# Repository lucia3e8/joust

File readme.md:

# joust!
- [ ] wands
    - [ ] enclosure design - 3d printed
    - [ ] electronics 
- [ ] base station
    - [ ] electronics

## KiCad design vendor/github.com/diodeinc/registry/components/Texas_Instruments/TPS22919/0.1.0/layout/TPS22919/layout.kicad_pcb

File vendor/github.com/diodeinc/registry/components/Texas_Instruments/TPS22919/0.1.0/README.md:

# TPS22919 — TI 5.5 V, 1.5 A load switch with controlled slew rate (SC-70-6)

Single gated power rail: TPS22919 plus input/output bypass, the QOD strap
that sets off-state discharge, and an external ON pull-down that makes the
rail default-off when nothing drives the enable.

## Parts

| `automotive` | MPN | Grade | Sourcing alternates |
|---|---|---|---|
| `False` (default) | TPS22919DCKR | catalog, −40 to 105 °C | TPS22919DCKT (250-pc reel) |
| `True` | TPS22919QDCKRQ1 | AEC-Q100 grade 1, −40 to 125 °C | — |

Both are SC-70-6 (DCK) with identical pinout and specifications. Slew rate
is fixed silicon; TI has no pin-compatible SC-70-6 sibling with a different
rise time. TPS22917 / TPS22918 add a CT pin for adjustable rise time but are
SOT-23-6 with a different pinout, so they need a separate package.

## Configuration

| Config | Type | Default | Effect |
|---|---|---|---|
| `automotive` | bool | `False` | Selects the AEC-Q100 orderable |
| `discharge` | `Internal` / `External` / `Off` | `Internal` | QOD strap: 0 Ω to VOUT, `r_qod` in series, or depopulated |
| `r_qod` | Resistance | `1kohm` | Series QOD resistance when `discharge="External"` |
| `c_in` | Capacitance | `1uF` | Input bypass (0402, 10 V) |
| `c_out` | Capacitance | `1uF` | Local output bypass (0402, 10 V); sets inrush = C × slew rate |
| `on_pulldown` | bool | `True` | Populate R_ON_PD |
| `on_pulldown_resistance` | Resistance | `100kohm` | R_ON_PD value |

## Examples

```zen
TPS22919 = Module("github.com/diodeinc/registry/components/Texas_Instruments/TPS22919/TPS22919.zen")

# microSD slot VDD, gated by an MCU GPIO. Default-off, fast discharge.
TPS22919(
    name="U_SD_PWR",
    VIN = V3V3,
    VOUT = V3V3_SD,
    GND = GND,
    ON = SD_PWR_EN,
)

# 5 V LED domain: extra local bulk, still discharged on gate-off.
TPS22919(
    name="U_LED_PWR",
    c_out = "10uF",
    VIN = V5,
    VOUT = V5_LED,
    GND = GND,
    ON = LED_PWR_EN,
)

# Slow the fall for power-down sequencing (R_DIS = 24 Ohm + r_qod).
TPS22919(
    name="U_SAT_PWR",
    discharge = "External",
    r_qod = "1kohm",
    VIN = V3V3,
    VOUT = V3V3_SAT,
    GND = GND,
    ON = SAT_PWR_EN,
)
```

## Integration notes

- `ON` thresholds (V_IH ≥ 1 V, V_IL ≤ 0.35 V) are referenced to GND, not
  VIN, so a 3.3 V GPIO can gate a 5 V rail. Keep V_ON ≤ 6 V.
- Default-off comes from the populated 100 kΩ R_ON_PD, not from the IC's
  Smart Pull Down, which disconnects permanently once ON is first driven
  high. Expect 33 µA at 3.3 V (55 µA at 5.5 V) of extra GPIO drive current
  while the rail is enabled.
- Turn-on takes 1.75–1.95 ms with a 2.7–3.2 mV/µs ramp. Inrush is
  C_LOAD × slew rate, so size total downstream bulk against what the
  upstream rail tolerates (47 µF ≈ 150 mA at 5 V).
- Off-state input current is 2 nA typ (800 nA max over temperature). There
  is no reverse blocking: the pass FET body diode conducts OUT → IN, so do
  not back-drive VOUT above VIN.
- 1.5 A continuous is a thermal limit, not an R_ON limit: R_θJA is
  210.7 °C/W in SC-70-6. Give the VIN/VOUT copper area at 1 A and above.
- The bundled `layout/TPS22919` fragment routes VIN, VOUT, QOD, and ON
  locally with 0.4 mm power copper and ties C_IN and R_ON_PD grounds
  together. C_OUT's ground pad is left for the parent board's ground plane.

## Package

**DCK / SC-70-6** (JEDEC MO-203 AB), 2.0 × 2.1 mm body, 0.65 mm pitch.
Footprint is KiCad's stock `SOT-363_SC-70-6` with an embedded STEP model —
1.025 × 0.35 mm pads on a 1.675 mm span, IPC-7351 nominal density. TI's
DCK0006A land pattern uses 0.9 × 0.4 mm pads on a 2.2 mm span; both reach a
3.1 mm outer envelope, with the KiCad pattern trading toe extension for
heel coverage.

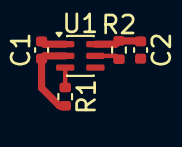
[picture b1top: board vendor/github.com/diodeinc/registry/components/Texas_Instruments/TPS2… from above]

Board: 2 copper layers, 5 parts (0 on the bottom side), 5 nets.

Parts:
C1, C2: GRM155Z71A105KE01D; C_0402_1005Metric
R1: ERJ-2RKF1003X; R_0402_1005Metric
R2: ERJ-2GE0R00X; R_0402_1005Metric
U1: TPS22919DCKR; SOT-363_SC-70-6

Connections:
GND: C1.2, C2.2, R1.2, U1.2
ON: R1.1, U1.3
QOD: R2.2, U1.5
VIN: C1.1, U1.1
VOUT: C2.1, R2.1, U1.6

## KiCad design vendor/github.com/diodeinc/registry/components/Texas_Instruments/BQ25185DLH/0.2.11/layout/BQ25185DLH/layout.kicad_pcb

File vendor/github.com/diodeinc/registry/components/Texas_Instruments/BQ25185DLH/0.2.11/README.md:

# BQ25185DLH

Texas Instruments BQ25185 1-cell, 1 A standalone **linear** Li-ion /
Li-poly / LiFePO₄ battery charger with integrated power path, pushbutton
input, and battery-tracking VINDPM. WSON-10 (DLH, 2.2 × 2.0 mm, exposed
pad). Orderable MPN: `BQ25185DLHR`.

- **VIN**: 2.7 V – 5.5 V recommended (25 V tolerant abs max)
- **ICHG**: 10 mA – 1000 mA, resistor programmed (R_ISET)
- **VBATREG**: 3.6 / 3.65 / 4.05 / 4.1 / 4.2 / 4.35 / 4.4 V (strap programmed)
- **ILIM**: 100 / 500 / 1100 mA (strap programmed, paired with VBATREG)
- **IDISCHG**: up to 3.125 A (BAT → SYS)

[Datasheet](https://www.ti.com/lit/ds/symlink/bq25185.pdf)

## Usage

```python
Bq25185 = Module("github.com/diodeinc/registry/components/Texas_Instruments/BQ25185DLH/BQ25185DLH.zen")

Bq25185(
    name="CHARGER",
    charge_current="500mA",
    battery_regulation="4.2V",
    input_current_limit="500mA",

    VIN=VBUS_5V,
    SYS=VSYS,
    BAT=VBAT_1S,
    GND=GND,

    CE=GND,          # tie low to always enable, or drive from a host GPIO
    STAT1=STAT1,     # optional open-drain status
    STAT2=STAT2,     # optional open-drain status
                     # TS omitted: bypass_thermistor=True handles it
)
```

### Dual-rate charging (XIAO HICHG-style) + no indicator LEDs

```python
Bq25185(
    name="CHARGER",
    charge_current="50mA",         # base rate (HICHG low / undriven)
    fast_charge_current="100mA",   # rate while HICHG is high
    populate_status_leds=False,    # drive your own charge LED from STAT

    VIN=VBUS_5V, SYS=VSYS, BAT=VBAT_1S, GND=GND,
    CE=GND,
    HICHG=HICHG,   # host GPIO ≥3 V: high = fast charge; undriven = base rate
    STAT1=STAT1,   # clean high-Z open-drain when LEDs depopulated
)
```

### Area-critical: omit unused optional footprints entirely

```python
Bq25185(
    name="CHARGER",
    charge_current="500mA",
    populate_status_leds=False,      # feature off
    disabled_circuitry="OMIT",       # drop the DNP footprints from the board

    VIN=VBUS_5V, SYS=VSYS, BAT=VBAT_1S, GND=GND,
    CE=GND,
    STAT1=STAT1,
)
```

With `disabled_circuitry="OMIT"` the disabled indicator-LED block
(D_STAT1/D_STAT2 + R_STAT1/R_STAT2) and, when `fast_charge_current` is
unset, the fast-charge block (R_ISET_FAST + Q_HICHG + R_HICHG_PD) are not
instantiated at all, so those footprints leave the board — useful when
every mm² of courtyard counts. The default (`"DNP"`) keeps them as
unpopulated footprints, unchanged from prior releases. When the
fast-charge branch is omitted, the `HICHG` gate io is not declared (it
gates the 2N7002, not a charger pin), so no dangling optional io and no
"`HICHG` not connected" warning results.

Setting `fast_charge_current` switches a second ISET resistor in parallel
through a 2N7002 N-FET (gate = `HICHG`, 100 kΩ pulldown parks the base
rate). It must be greater than `charge_current` and ≤ 1000 mA. Leaving it
unset keeps a single fixed rate. Drive `HICHG` at ≥ 3 V (2N7002
V_GS(th) up to 2.5 V) — a 1.8 V GPIO is not guaranteed to enable fast
charge. `populate_status_leds=False` DNPs the D_STAT1/D_STAT2 LEDs and
their 1.2 kΩ resistors (topology preserved).

Invalid (`battery_regulation`, `input_current_limit`) combinations fail
the build — only the pairs in datasheet Table 7-1 are valid (100 mA ILIM
exists only with V_BATREG = 4.2 V).

## Integration notes

- `CE` must not float; there is intentionally no internal strap.
- With an external NTC on `TS`, set `bypass_thermistor=False` or the
  populated 10 kΩ bypass shifts the hot/cold trip points.
- By default STAT1/STAT2 drive a status LED (red/orange) through a
  1.2 kΩ current-limit resistor from SYS (~1.9 mA). This is an
  indication path, not a clean GPIO pull-up: for host readback add a
  pull-up to the host logic rail and use a SYS-tolerant / high-Z input.
  Set `populate_status_leds=False` to DNP the LEDs and resistors, which
  also leaves STAT as an unloaded high-Z open-drain node.
- `disabled_circuitry` (`"DNP"` default / `"OMIT"`) chooses whether a
  switched-off optional block (indicator LEDs, or the fast-charge branch
  when `fast_charge_current` is unset) is DNP-placed or dropped from the
  board entirely. Use `"OMIT"` only on area-critical designs where the
  feature is permanently unused.
- ESD/TVS on VIN, cell-level battery protection, and USB BC1.2 detection
  are integrator-owned (see the `.zen` docstring).
- Footprint follows the TI DLH0010A datasheet land pattern (pads
  0.5 × 0.2 mm at ±0.8 mm, 0.9 × 1.5 mm exposed pad, ~88 % paste
  coverage on the EP) with the vendor STEP model embedded.

## Migration notes

Both additions in v0.3 are backward compatible — with `fast_charge_current`
unset and `populate_status_leds` at its `True` default, the netlist,
BOM population, and behavior are identical to prior versions.

- **`fast_charge_current` (optional `Current`)** + **`HICHG` (optional
  `Net`)**: adds a DNP-by-default dual-rate ISET branch (R_ISET_FAST +
  2N7002 + 100 kΩ gate pulldown). Populated only when
  `fast_charge_current` is set; requires `charge_current` <
  `fast_charge_current` ≤ 1000 mA. Drive `HICHG` at ≥ 3 V; it may be left
  unconnected (held low = base rate). Adds a dependency on
  `components/2N7002` (DNP unless the feature is enabled).
- **`populate_status_leds` (`bool`, default `True`)**: set `False` to
  DNP the indicator LEDs and their series resistors. No action needed to
  retain the previous always-populated behavior.

The following add one config and shrink one passive:

- **`disabled_circuitry` (enum `"DNP"` | `"OMIT"`, default `"DNP"`)**:
  when set to `"OMIT"`, a *disabled* optional block (indicator LEDs when
  `populate_status_leds=False`; fast-charge branch when
  `fast_charge_current` is unset) is not instantiated, removing its
  footprints from the board for area-critical consumers. The `"DNP"`
  default preserves the prior DNP-placed behavior, topology, netlist and
  BOM population unchanged from prior versions. When the fast-charge
  branch is omitted (`disabled_circuitry="OMIT"` with `fast_charge_current`
  unset), the `HICHG` gate io is now declared only when that branch
  exists, so it no longer emits a "`HICHG` not connected to any ports"
  warning. This is a diagnostic-only fix: consumers that set
  `fast_charge_current` and/or connect `HICHG` are unaffected (the io is
  still exposed whenever the branch is populated or DNP-placed).
- **C_BAT downsized 0603 → 0402** (intentional passive change — the
  C_BAT MPN and footprint differ from prior versions): now a
  2.2 µF / 25 V / X5R 0402 (Murata GRM155R61E225KE11D). Datasheet
  §8.2.2.3 requires only 1 µF on BAT with no 25 V callout (the 25 V
  recommendation is scoped to IN/SYS). BAT tops at V_BATREG (≤ 4.4 V),
  where the 25 V-rated 0402 holds ≈ 1.35–1.39 µF on Murata typical
  DC-bias data — above the 1 µF floor and above the 1 µF TI uses in its
  own characterization, though with less headroom than the 0603.
  C_VIN (0603) and C_SYS (0805) were reviewed and deliberately left
  unchanged. Re-sync your layout so the C_BAT footprint updates to 0402.
- **Strap/signal resistors downsized 0402 → 0201** (footprint/BOM change,
  no API change): R_ISET, R_VSET, R_TS_BYPASS, R_ISET_FAST, R_HICHG_PD,
  R_STAT1, R_STAT2 now use house Panasonic ERJ-1GNF/ERJ-1GJF 0201
  (25 V / 0.05 W / 1 %). Node voltages (≤ 5 V) and dissipation (≤ ~5 mW)
  sit well inside the 0201 ratings, and R_ISET/R_VSET keep their 1 %
  tolerance so charge-current / regulation accuracy is unchanged.
  **C_ISET stays 0402**: the house cap catalog has no 0201 C0G part
  (0201 tops out at 2.2 nF X7R), so a C0G 47 pF is only sourceable at
  0402. C_VIN/C_SYS/C_BAT are unchanged (§8.2.2.3 voltage-rating /
  derating). Re-sync your layout for the 0201 resistor footprints.

## Supersedes

This package replaces `components/Texas_Instruments/BQ25185DLHR` and
`reference/BQ25185x` (deprecated: non-datasheet pin names, thermal pad
modeled as a second GND pin, and perimeter pads shifted 0.25 mm outboard
of the TI land pattern).

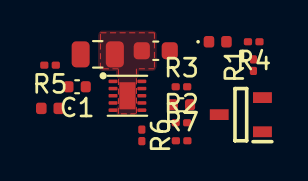
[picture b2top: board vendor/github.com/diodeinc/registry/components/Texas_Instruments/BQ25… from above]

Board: 2 copper layers, 15 parts (0 on the bottom side), 13 nets, no tracks yet.

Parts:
C1: GRM155R61E225KE11D; C_0402_1005Metric
C2: GCM1555C1H470FA16D; C_0402_1005Metric
C3: GRM21BZ71E106KE15K; C_0805_2012Metric
C4: GRM188Z71E225ME43D; C_0603_1608Metric
D1: VLMS1500-GS08; LED_0402_1005Metric
D2: VLMO1500-GS08; LED_0402_1005Metric
Q1: 2N7002; SOT95P260X110-3N
R1: ERJ-1GJF1003C; R_0201_0603Metric
R2, R3: ERJ-1GJF1001C; R_0201_0603Metric
R4, R5: ERJ-1GJF1201C; R_0201_0603Metric
R6: ERJ-1GJF1002C; R_0201_0603Metric
R7: ERJ-1GJF1802C; R_0201_0603Metric
U1: BQ25185DLHR; BQ25185DLH

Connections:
BAT: C1.1, U1.2
GND: C1.2, C2.2, C3.2, C4.2, Q1.2, R1.2, R2.2, R6.2, R7.2, U1.5, U1.11
HICHG: Q1.1, R1.1
ILIM_VSET: R7.1, U1.7
ISET: C2.1, R2.1, R3.1, U1.8
ISET_FAST: Q1.3, R3.2
STAT1: D1.1, U1.9
STAT1_LED_A: D1.2, R4.2
STAT2: D2.1, U1.3
STAT2_LED_A: D2.2, R5.2
SYS: C3.1, R4.1, R5.1, U1.1
TS: R6.1, U1.6
VIN: C4.1, U1.10

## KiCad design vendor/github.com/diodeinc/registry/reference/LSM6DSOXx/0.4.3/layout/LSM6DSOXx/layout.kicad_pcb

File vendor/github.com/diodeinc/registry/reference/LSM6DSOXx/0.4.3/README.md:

# LSM6DSOXx Reference Design

Reference design for the STMicroelectronics LSM6DSOXTR, a 6-axis IMU with embedded AI
(Machine Learning Core + Finite State Machine). Implements Mode 1 configuration with
selectable I²C or SPI primary interface.

## Features
- **IC**: LSM6DSOXTR (LGA-14L, 2.5 × 3.0 × 0.83 mm)
  - 3-axis accelerometer: ±2/±4/±8/±16 g
  - 3-axis gyroscope: ±125/±250/±500/±1000/±2000 dps
  - 0.55 mA combo high-performance mode, 3 µA power-down
  - Embedded finite state machine (16 programs) and machine learning core (8 decision trees)
  - 9 KB smart FIFO with compression
- **Interfaces**: I²C (up to 400 kHz) or SPI (up to 10 MHz), selectable via config
- **Interrupts**: Two programmable interrupt outputs (INT1, INT2)
## Usage

### I²C mode (default)

```python
LSM6DSOXx = Module("github.com/diodeinc/registry/reference/LSM6DSOXx/LSM6DSOXx.zen")

LSM6DSOXx(
    name="IMU",
    VDD=vdd_1v8,
    VDDIO=vddio_1v8,
    GND=gnd,
    I2C=i2c_bus,
    i2c_address="0x6A",
    INT1=imu_int1,
)
```

### SPI mode

```python
LSM6DSOXx = Module("github.com/diodeinc/registry/reference/LSM6DSOXx/LSM6DSOXx.zen")

LSM6DSOXx(
    name="IMU",
    communication="SPI",
    VDD=vdd_1v8,
    VDDIO=vddio_1v8,
    GND=gnd,
    SPI=spi_bus,
    INT1=imu_int1,
    INT2=imu_int2,
)
```

## Design Notes

- **Mode 1 only**: SDX and SCX pins are tied to GND via 0 Ω resistors (per datasheet
  Section 7.1). Modes 2–4 (sensor hub, auxiliary SPI / OIS) are not supported.
- **OCS_AUX / SDO_AUX**: Left unconnected per Mode 1 requirements. Internal pull-ups
  are enabled by default in Mode 1 (Table 20).
- **Decoupling**: 100 nF ceramic on each supply pin, placed close to the IC per
  datasheet recommendation (Section 7.1).
- **CS pull-up**: 10 kΩ to VDDIO. In I²C mode, holds CS high to select the I²C
  interface. In SPI mode, keeps CS deasserted at reset until the master drives it.
- **I²C pull-ups**: 4.7 kΩ to VDDIO. The I²C interface requires external pull-ups on
  SCL and SDA (Section 5.1.1). Set `i2c_pullup=False` if pull-ups are provided
  elsewhere on the bus.
- **I²C address**: Configured via `i2c_address`. A 10 kΩ resistor straps SDO/SA0
  to GND (0x6A) or VDDIO (0x6B). Both resistors DNP in SPI mode.

## References
- [LSM6DSOX Datasheet](https://www.st.com/resource/en/datasheet/lsm6dsox.pdf)
- [AN5272 — LSM6DSOX Application Note](https://www.st.com/resource/en/application_note/an5272.pdf)

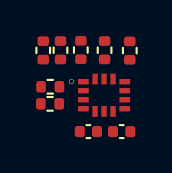
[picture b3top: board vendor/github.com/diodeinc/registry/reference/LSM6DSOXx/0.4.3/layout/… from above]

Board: 2 copper layers, 10 parts (0 on the bottom side), 9 nets, no tracks yet.

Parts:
C1, C2: GCM155R71H104KE02D; C_0402_1005Metric
R1, R2, R3: ERJ-2RKF1002X; R_0402_1005Metric
R4, R6: ERJ-2RKF4701X; R_0402_1005Metric
R5, R7: ERJ-2GE0R00X; R_0402_1005Metric
U1: LSM6DSOXTR

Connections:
CS: R1.1, U1.12
GND: C1.2, C2.2, R3.2, R5.2, R7.2, U1.6, U1.7
I2C_SCL: R4.1, U1.13
I2C_SDA: R6.1, U1.14
SCX: R5.1, U1.3
SDX: R7.1, U1.2
SPI_MISO: R2.1, R3.1, U1.1
VDD: C1.1, U1.8
VDDIO: C2.1, R1.2, R2.2, R4.2, R6.2, U1.5

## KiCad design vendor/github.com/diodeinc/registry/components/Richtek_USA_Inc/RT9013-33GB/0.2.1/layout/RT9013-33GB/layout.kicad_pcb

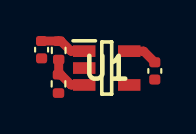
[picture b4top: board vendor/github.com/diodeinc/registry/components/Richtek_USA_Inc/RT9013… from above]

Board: 2 copper layers, 5 parts (0 on the bottom side), 4 nets.

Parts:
C1, C2: GRM155Z71A105KE01D; C_0402_1005Metric
R1, R2: ERJ-2RKF1003X; R_0402_1005Metric
U1: RT9013-33GB; SOT94P279X130-5N

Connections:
EN: R1.1, R2.1, U1.3
GND: C1.2, C2.2, R1.2, U1.2
VIN: C1.1, R2.2, U1.1
VOUT: C2.1, U1.5

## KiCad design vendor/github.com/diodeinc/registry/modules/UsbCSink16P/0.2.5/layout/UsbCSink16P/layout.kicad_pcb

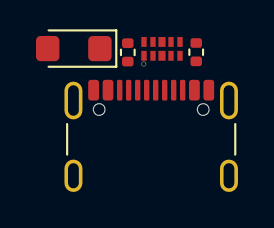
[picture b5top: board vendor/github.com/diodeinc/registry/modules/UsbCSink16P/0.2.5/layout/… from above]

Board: 2 copper layers, 5 parts (0 on the bottom side), 6 nets, no tracks yet.

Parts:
D1: SMF5V0A-E3; D_SMF
IC1: TPD4E05U06QDQARQ1; DQA_R-PUSON-N10_
J1: USB4105-GF-A; USB_C_Receptacle_GCT_USB4105-xx-A_16P_TopMnt_Horizontal
R1, R2: ERJ-2RKF5101X; R_0402_1005Metric

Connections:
GND: D1.2, IC1.3, IC1.8, J1.A1, J1.A12, J1.B1, J1.B12, J1.S1, R1.2, R2.2
USB_C_CC1: IC1.1, IC1.10, J1.A5, R1.1
USB_C_CC2: IC1.5, IC1.6, J1.B5, R2.1
USB_C_D_N: IC1.2, IC1.9, J1.A7, J1.B7
USB_C_D_P: IC1.4, IC1.7, J1.A6, J1.B6
VBUS: D1.1, J1.A4, J1.A9, J1.B4, J1.B9

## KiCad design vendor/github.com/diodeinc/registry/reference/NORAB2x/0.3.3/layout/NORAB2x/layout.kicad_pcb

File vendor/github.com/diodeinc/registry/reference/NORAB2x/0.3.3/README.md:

# NORAB2x Reference Design

u-blox NORA-B2 Bluetooth LE and IEEE 802.15.4 module reference circuit for the
NORA-B206-00B (integrated PCB trace antenna variant). Based on the Nordic
Semiconductor nRF54L15 SoC.

## Features

- **IC**: u-blox NORA-B206-00B (LGA, 14.3 × 10.4 × 1.9 mm)
  - Bluetooth 6.0 LE, IEEE 802.15.4 (Thread, Matter, Zigbee)
  - Arm Cortex-M33 (128 MHz) + RISC-V coprocessor (128 MHz)
  - 256 kB RAM, 1.5 MB flash
  - Integrated PCB trace antenna (+3 dBi)
  - Channel Sounding support
- **Supply**: 1.7V to 3.5V single rail with VCC decoupling
- **Interfaces**: UART, SPI (32 MHz), QSPI, I2C, SWD, NFC, 8× GPIO
- **Clock**: Optional 32.768 kHz crystal for lowest-power LFCLK
- **Reset**: Internal ~14 kΩ pull-up; 100 nF input cap for noise filtering; 0 Ω series resistor for external reset access
- **I2C**: Optional 10 kΩ pull-up resistors to VCC

## Interfaces

| Name | Type | Description |
|------|------|-------------|
| VCC | Power | Module supply (1.7V to 3.5V) |
| GND | Ground | Common ground |
| UART | Uart | UART data (TX/RX, module perspective) |
| UART_RTS | Gpio | UART request-to-send (optional) |
| UART_CTS | Gpio | UART clear-to-send (optional) |
| SPI | Spi | SPI main node, up to 32 MHz (optional) |
| SPI_DCX | Gpio | SPI Data/Command for displays (optional) |
| QSPI | Qspi | Quad SPI for external flash (optional) |
| I2C | I2c | I2C bus (optional) |
| SWD | Swd | Serial Wire Debug |
| RESET_N | Net | Active-low reset input (optional) |
| NFC1, NFC2 | Net | NFC antenna pads (optional) |
| GPIO_P0_00–GPIO_P1_13 | Gpio | 8 general-purpose IOs (optional) |
| WAKE_HOST | Gpio | Module-to-host wake (optional) |
| WAKE_UP | Gpio | Host-to-module wake (optional) |

## Configuration

| Parameter | Type | Default | Description |
|-----------|------|---------|-------------|
| populate_crystal | bool | True | Populate 32.768 kHz crystal (Y_LFXO). False DNPs the crystal and uses internal RC (~500 ppm). |
| i2c_pullup | bool | True | Populate I2C pull-up resistors (10 kΩ to VCC). |

## Usage

```python
NORAB2x = Module("github.com/diodeinc/registry/reference/NORAB2x/NORAB2x.zen")

NORAB2x(
    name="U1",
    VCC=vcc_3v3,
    GND=gnd,
    UART=uart_bus,
    SWD=swd_bus,
    I2C=i2c_bus,
)
```

### Minimal BLE beacon (UART + SWD only)

```python
NORAB2x(
    name="U1",
    VCC=vcc_3v3,
    GND=gnd,
    SWD=swd_bus,
    populate_crystal=True,
)
```

### With external QSPI flash and no crystal

```python
NORAB2x(
    name="U1",
    VCC=vcc_1v8,
    GND=gnd,
    UART=uart_bus,
    SWD=swd_bus,
    QSPI=qspi_flash_bus,
    populate_crystal=False,
)
```

## Design Notes

### Pin Sharing
Two GPIO pins are internally connected to RF control pins on the module:
- `GPIO_P0_02` ↔ `RF_CTRL2` (pads C8 and G7, both nRF P0.02)
- `GPIO_P1_13` ↔ `RF_CTRL1` (pads J8 and G5, both nRF P1.13)

The reference design connects each pair to the same net so the integrator
gets a single IO per physical nRF pin.

### Antenna
NORA-B206 has an integrated PCB trace antenna. The host PCB must:
- Place the module centered on a board edge
- Provide ≥10 mm ground plane on three non-edge sides
- Include a ground-plane cutout under the antenna area
- Maintain ≥10 mm clearance from tall components and enclosure walls
- Connect all EAGP pads to ground with stitching vias

### Low-Frequency Clock
- **populate_crystal=True** (default): 32.768 kHz crystal provides ±20 ppm accuracy and lowest
  sleep current. Configure in firmware via device tree `&hfxo` and `&lfxo` nodes.
- **populate_crystal=False**: Crystal is DNP. Internal RC oscillator (LFRC, ~500 ppm). Pins XL1/XL2 become
  available as GPIOs (P1.00, P1.01). Slightly higher sleep current but simpler BOM.

### Reset Circuit
The module has an internal ~14 kΩ pull-up on RESET_N (typ 14 kΩ, range 12–16 kΩ per
datasheet Table 18). No external pull-up is needed. A 100 nF cap to ground filters
noise and provides a power-on delay (RC ≈ 1.4 ms with the internal 14 kΩ). A 0 Ω
series resistor (`R_RESET_EXT`) connects the `RESET_N` IO for external reset control
via open-drain driver or push button.

### HFXO Internal Load Capacitance
The internal 32 MHz crystal requires software configuration of internal load caps.
Add this to your Zephyr device tree board definition:
```dts
&hfxo {
    load-capacitors = "internal";
    load-capacitance-femtofarad = <14250>;
};
```

### NFC
To use NFC, connect NFC1 and NFC2 to an inductive NFC antenna with tuning capacitors
for 13.56 MHz resonance. When not using NFC, NFC1/NFC2 can be configured as GPIOs
(P1.02, P1.03) in firmware — but do not apply an NFC field when in GPIO mode.

## References

- [NORA-B2 Data Sheet](https://content.u-blox.com/sites/default/files/NORA-B2_DataSheet_UBX-23013817.pdf) (UBX-23013817)
- [NORA-B2 System Integration Manual](https://content.u-blox.com/sites/default/files/documents/NORA-B2_SIM_UBXDOC-465451970-3345.pdf) (UBXDOC-465451970-3345)
- [nRF54L15 Datasheet](https://docs.nordicsemi.com/bundle/ps_nrf54L15/page/keyfeatures_html5.html) (Nordic Semiconductor)
- [nRF Connect SDK](https://developer.nordicsemi.com/nRF_Connect_SDK/doc/latest/nrf/index.html)

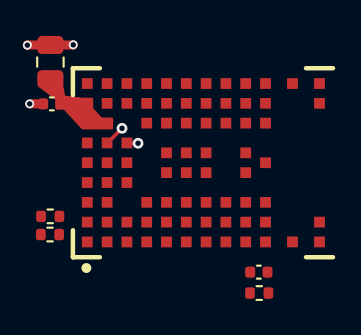
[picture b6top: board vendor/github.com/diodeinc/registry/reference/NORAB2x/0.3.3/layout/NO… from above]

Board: 2 copper layers, 8 parts (1 on the bottom side), 9 nets.

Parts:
C1, C2: GCM155R71H104KE02D; C_0402_1005Metric
C3: GRM21BZ71E106KE15K; C_0805_2012Metric
R1: ERJ-2GE0R00X; R_0402_1005Metric
R2, R3: ERJ-2RKF1002X; R_0402_1005Metric
U1: ?; NORA-B206-00B
Y1: 32.768kHz 7pF; Crystal_SMD_3215-2Pin_3.2x1.5mm

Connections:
GND: C1.2, C2.2, C3.2, U1.A1, U1.A9, U1.B2, U1.B8, U1.E4, U1.E5, U1.F4, U1.F5, U1.K2, U1.K3, U1.K5, U1.K7, U1.K8, U1.L1, U1.L9, U1.M1, U1.M2, U1.M8, U1.M9
GPIO_P0_02: U1.C8, U1.G7
GPIO_P1_13: U1.G5, U1.J8
I2C_SCL: R2.1, U1.A3
I2C_SDA: R3.1, U1.B4
RST: C1.1, R1.2, U1.J3
VCC: C2.1, C3.1, R2.2, R3.2, U1.A7, U1.A8, U1.B7
XL1: U1.B6, Y1.1
XL2: U1.C6, Y1.2

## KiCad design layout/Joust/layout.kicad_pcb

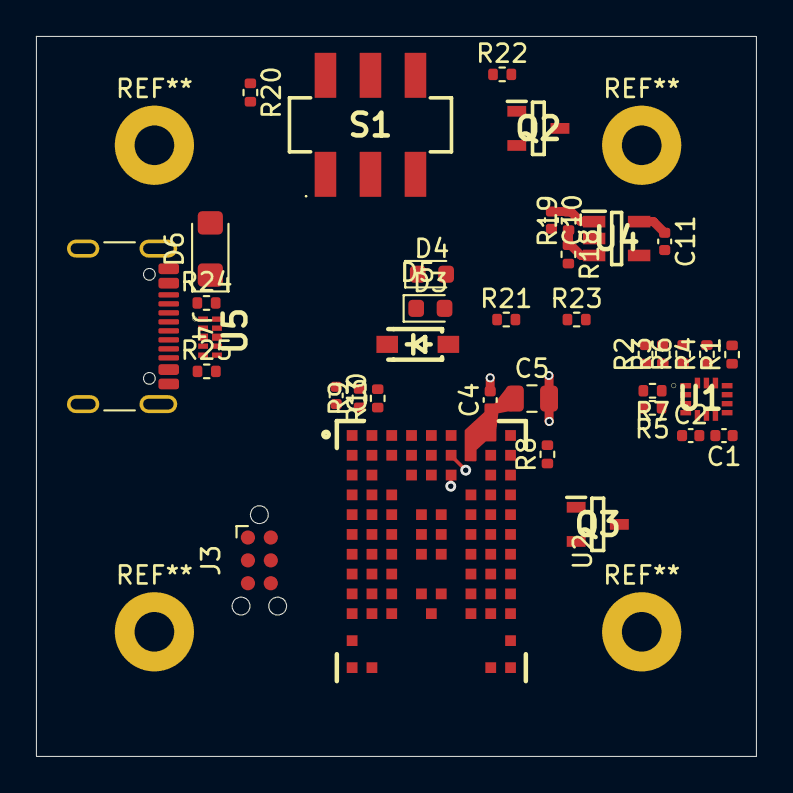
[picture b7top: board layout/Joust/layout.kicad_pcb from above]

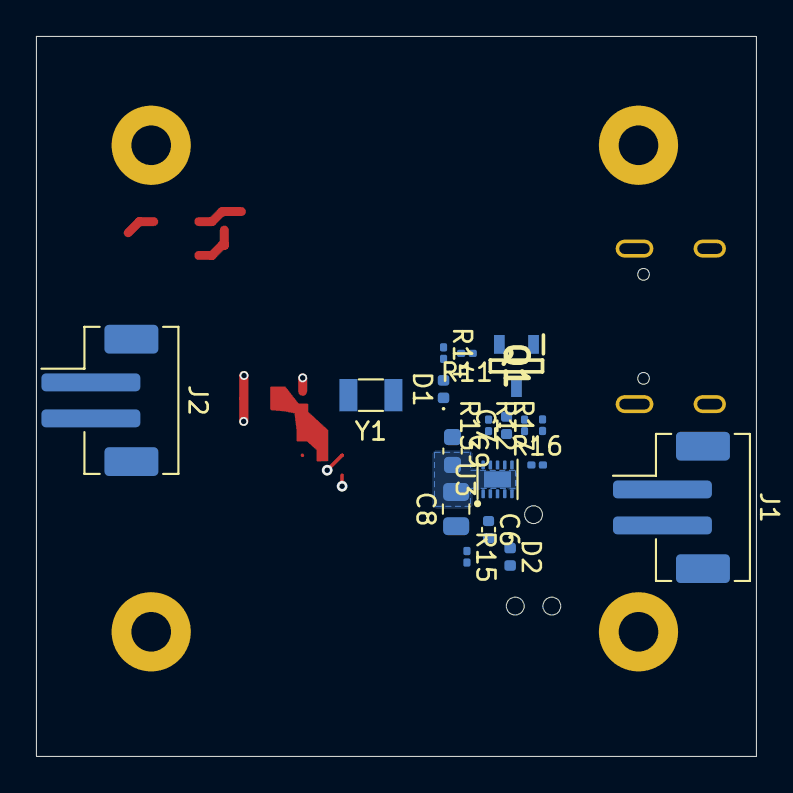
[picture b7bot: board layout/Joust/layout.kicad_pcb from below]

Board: 2 copper layers, 40.0 x 40.0 mm, 56 parts (18 on the bottom side), 40 nets.

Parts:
C1, C2, C3, C4: GCM155R71H104KE02D; C_0402_1005Metric
C5, C8: GRM21BZ71E106KE15K; C_0805_2012Metric
C6: GRM155R61E225KE11D; C_0402_1005Metric
C7: GCM1555C1H470FA16D; C_0402_1005Metric
C9: GRT188R61H225KE13D; C_0603_1608Metric
C10, C11: GRM155Z71A105KE01D; C_0402_1005Metric
D1: VLMS1500-GS08; LED_0402_1005Metric
D2: VLMO1500-GS08; LED_0402_1005Metric
D3, D4: KP-1608SURCK; LED_0603_1608Metric
D5: 1N4148W-7-F
D6: SMF5V0A-E3; D_SMF
J1, J2: B2B-PH-SM4-TB; JST_PH_B2B-PH-SM4-TB_1x02-1MP_P2.00mm_Vertical
J3: TC2030-IDC-NL; Tag-Connect_TC2030-IDC-NL_2x03_P1.27mm_Vertical
J4: USB4105-GF-A; USB_C_Receptacle_GCT_USB4105-xx-A_16P_TopMnt_Horizontal
Q1, Q2, Q3: 2N7002KT1G; SOT95P260X110-3N
R1, R2, R3, R9, R10: ERJ-2RKF1002X; R_0402_1005Metric
R4, R6: ERJ-2RKF4701X; R_0402_1005Metric
R5, R7, R8: ERJ-2GE0R00X; R_0402_1005Metric
R11: ERJ-1GJF1003C; R_0201_0603Metric
R12, R13: ERJ-1GJF2371C; R_0201_0603Metric
R14, R15: ERJ-1GJF1201C; R_0201_0603Metric
R16: ERJ-1GJF1002C; R_0201_0603Metric
R17: ERJ-1GJF1802C; R_0201_0603Metric
R18, R19, R22, R23: ERJ-2RKF1003X; R_0402_1005Metric
R20, R21: ERJ-2RKF1200X; R_0402_1005Metric
R24, R25: ERJ-2RKF5101X; R_0402_1005Metric
S1: JS202011SCQN
U1: LSM6DSOXTR
U2: NORA-B206-00B
U3: BQ25185DLHR; BQ25185DLH
U4: RT9013-33GB; SOT94P279X130-5N
U5: TPD4E05U06QDQARQ1; DQA_R-PUSON-N10_
Y1: 32.768kHz 7pF; Crystal_SMD_3215-2Pin_3.2x1.5mm

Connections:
ACC.CS: R1.1, U1.12
ACC.SCX: R5.1, U1.3
ACC.SDX: R7.1, U1.2
ACC.SPI_MISO: R2.1, R3.1, U1.1
ACC_INT: U1.4, U2.H8
BLE.GPIO_P0_02: U2.C8, U2.G7
BLE.GPIO_P1_13: U2.G5, U2.J8
BLE.RST: C3.1, R8.2, U2.J3
BLE.XL1: U2.B6, Y1.1
BLE.XL2: U2.C6, Y1.2
CHG.HICHG: Q1.1, R11.1
CHG.ILIM_VSET: R17.1, U3.7
CHG.ISET: C7.1, R12.1, R13.1, U3.8
CHG.ISET_FAST: Q1.3, R13.2
CHG.STAT1: D1.1, U3.9
CHG.STAT1_LED_A: D1.2, R14.2
CHG.STAT2: D2.1, U3.3
CHG.STAT2_LED_A: D2.2, R15.2
CHG.TS: R16.1, U3.6
GND: C1.2, C2.2, C3.2, C4.2, C5.2, C6.2, C7.2, C8.2, C9.2, C10.2, C11.2, D6.2, J1.2, J1.MP, J2.MP, J3.5, J4.A1, J4.A12, J4.B1, J4.B12, J4.S1, Q1.2, Q2.2, Q3.2, R3.2, R5.2, R7.2, R11.2, R12.2, R16.2, R17.2, R18.2, R22.2, R23.2, R24.2, R25.2, S1.3, S1.6, U1.6, U1.7, U2.A1, U2.A9, U2.B2, U2.B8, U2.E4, U2.E5, U2.F4, U2.F5, U2.K2, U2.K3, U2.K5, U2.K7, U2.K8, U2.L1, U2.L9, U2.M1, U2.M2, U2.M8, U2.M9, U3.4, U3.5, U3.11, U4.2, U5.3, U5.8
I2C_SCL: R4.1, R9.1, U1.13, U2.A3
I2C_SDA: R6.1, R10.1, U1.14, U2.B4
LDO_EN: R18.1, R19.1, S1.2, S1.5, U4.3
LED1_A: D3.2, R20.2
LED2_A: D4.2, R21.2
LED_GATE: Q2.1, R22.1, U2.H9
LED_K: D3.1, D4.1, Q2.3
MOT_GATE: Q3.1, R23.1, U2.D8
MOT_SW: D5.2, J2.2, Q3.3
RESET_N: J3.3, R8.1
SWD_SWCLK: J3.4, U2.J2
SWD_SWDIO: J3.2, U2.H2
USB_C_CC1: J4.A5, R24.1, U5.1, U5.10
USB_C_CC2: J4.B5, R25.1, U5.5, U5.6
USB_C_D_N: J4.A7, J4.B7, U5.2, U5.9
USB_C_D_P: J4.A6, J4.B6, U5.4, U5.7
V3V3: C1.1, C2.1, C4.1, C5.1, C11.1, J3.1, R1.2, R2.2, R4.2, R6.2, R9.2, R10.2, U1.5, U1.8, U2.A7, U2.A8, U2.B7, U4.5
VBAT: C6.1, J1.1, U3.2
VBUS: C9.1, D6.1, J4.A4, J4.A9, J4.B4, J4.B9, U3.10
VSYS: C8.1, C10.1, D5.1, J2.1, R14.1, R15.1, R19.2, R20.1, R21.1, S1.1, S1.4, U3.1, U4.1
